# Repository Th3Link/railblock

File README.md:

# RailBlock

[![Firmware License:
GPLv3](https://img.shields.io/badge/Firmware-GPLv3-blue.svg)]()
[![Hardware License: CERN-OHL-S
v2](https://img.shields.io/badge/Hardware-CERN--OHL--S%20v2-orange.svg)]()

**RailBlock** is an open hardware CAN‑bus based block detector and
signal controller for model railways.

It is designed to integrate with a **Raspberry Pi running Rocrail**,
providing reliable **track occupancy detection** and **signal control**
using a distributed CAN bus network.

The project consists of:

-   **Hardware** -- KiCad PCB design
-   **Firmware** -- written in **Embedded Rust** using **Embassy** and
    **heapless**

------------------------------------------------------------------------

# Overview

RailBlock modules are connected using a **50 kbit/s CAN bus** carried
over **RJ45 cables**.\
Each board contains:

-   an **ESP32 microcontroller**
-   a **CAN transceiver**
-   inputs for **Hall sensors**
-   outputs for **signal lights**

Multiple boards can be connected in a **daisy-chain topology**,
distributing both **power (12V)** and **CAN communication** over a
single cable.

Typical setup:

    Raspberry Pi (Rocrail)
            │
       CAN Interface
            │
      ───── CAN Bus ─────
         │       │       │
     RailBlock RailBlock RailBlock
         │       │       │
     Sensors   Signals  Sensors

------------------------------------------------------------------------

# Features

-   CAN bus communication (**50 kbit/s**)
-   RJ45 bus connectors for **daisy chaining**
-   **Power + data on one cable**
-   Up to **3 Hall sensors** per board
-   Up to **7 signal outputs**
-   **ULN2003A sinking driver**
-   **ESP32 microcontroller**
-   **Embedded Rust firmware**
-   **JTAG debugging support**
-   Designed for **Rocrail integration**

------------------------------------------------------------------------

# Hardware

The hardware design is provided as a **KiCad project**.

Each RailBlock node contains:

-   ESP32 microcontroller
-   CAN transceiver
-   ULN2003A output driver
-   connectors for Hall sensors
-   connectors for signal lights
-   two RJ45 bus connectors

The RJ45 connectors allow the bus to **pass through each board**,
simplifying wiring.

Both **power and CAN signals** are carried through the same cable.

------------------------------------------------------------------------

# RJ45 Bus Pinout

RailBlock uses standard **RJ45 connectors** to distribute **CAN bus and
12V power**.

Multiple pins are paralleled to increase current capacity.

    RJ45 Pinout (RailBlock Bus)

       +-----------------------+
       | 1  2  3  4  5  6  7  8 |
       +-----------------------+

    Pin 1  ── GND
    Pin 2  ── GND
    Pin 3  ── GND

    Pin 4  ── CANH
    Pin 5  ── CANL

    Pin 6  ── +12V
    Pin 7  ── +12V
    Pin 8  ── +12V

Notes:

-   Pins **4 and 5 form a twisted pair** in standard Ethernet cables
    (blue / blue‑white).
-   Pins **1--3 and 6--8 are bundled** to increase current carrying
    capacity.
-   This allows moderate **power distribution along the bus**.

------------------------------------------------------------------------

# Bus Topology

RailBlock nodes must be connected in a **linear CAN topology**.

    12V + CAN Bus

    [Terminator] ── RailBlock ── RailBlock ── RailBlock ── [Terminator]

Important:

-   The **first and last node must be terminated**.
-   Termination uses the standard **120 Ω CAN resistor**.

------------------------------------------------------------------------

# Inputs -- Hall Sensors

Each RailBlock board supports **up to 3 Hall sensors** for track
occupancy detection.

Recommended sensor:

-   **TLE4905L**
-   or compatible digital Hall sensors

Typical setup:

-   a small magnet is mounted under a locomotive
-   the Hall sensor detects the magnet
-   the RailBlock node sends an occupancy event

Events are transmitted over CAN using **S88 event messages**.

------------------------------------------------------------------------

# Outputs -- Signals

Each RailBlock board supports **up to 7 signal outputs**.

Outputs are implemented using a **ULN2003A Darlington driver**.

The LED anode connects to **+12V or +5V via a resistor**, while the
RailBlock output sinks current. Some signals have internal resistors.

------------------------------------------------------------------------

# Firmware

The firmware is written in **Embedded Rust**.

Technologies used:

-   **Embassy** async runtime
-   **heapless** containers (no dynamic allocation)
-   **esp-hal**

Design goals:

-   deterministic behaviour
-   low memory usage
-   robust CAN communication

------------------------------------------------------------------------

# CAN Protocol

RailBlock communicates over CAN using two protocol types.

## Märklin CS2 Accessory Protocol

Used for:

-   signal control
-   accessory commands

## S88 Event Messages

Used to report:

-   Hall sensor triggers
-   block occupancy events

------------------------------------------------------------------------

# Programming and Debugging

The ESP32 firmware can be uploaded using:

### Programming Adapter

A dedicated **programming adapter** (separate project).

### JTAG

The board also supports **JTAG debugging**, allowing:

-   breakpoints
-   single stepping
-   real runtime debugging

------------------------------------------------------------------------

# Integration with Rocrail

RailBlock is designed to work with **Rocrail** running on a **Raspberry
Pi**.

Typical architecture:

    Raspberry Pi
       (Rocrail)
           │
       CAN Interface
           │
      ───── CAN Bus ─────
         │       │       │
     RailBlock RailBlock RailBlock
         │       │       │
     Sensors   Signals  Sensors

Rocrail can:

-   receive **occupancy events**
-   control **signals and accessories**

------------------------------------------------------------------------

# Repository Structure

    railblock/
    │
    ├─ firmware/        Embedded Rust firmware
    │
    ├─ hardware/        KiCad PCB design
    │
    ├─ docs/            Documentation
    │
    └─ README.md

------------------------------------------------------------------------

# Licensing

This repository contains both **hardware designs** and **software**.

## Firmware

Licensed under:

**GNU General Public License v3 (GPLv3)**

See:

    firmware/LICENSE.txt

## Hardware

Licensed under:

**CERN Open Hardware Licence Version 2 -- Strongly Reciprocal
(CERN-OHL-S-2.0)**

See:

    hardware/LICENSE.txt

------------------------------------------------------------------------

# Status

Early development.

Hardware and firmware are evolving together.

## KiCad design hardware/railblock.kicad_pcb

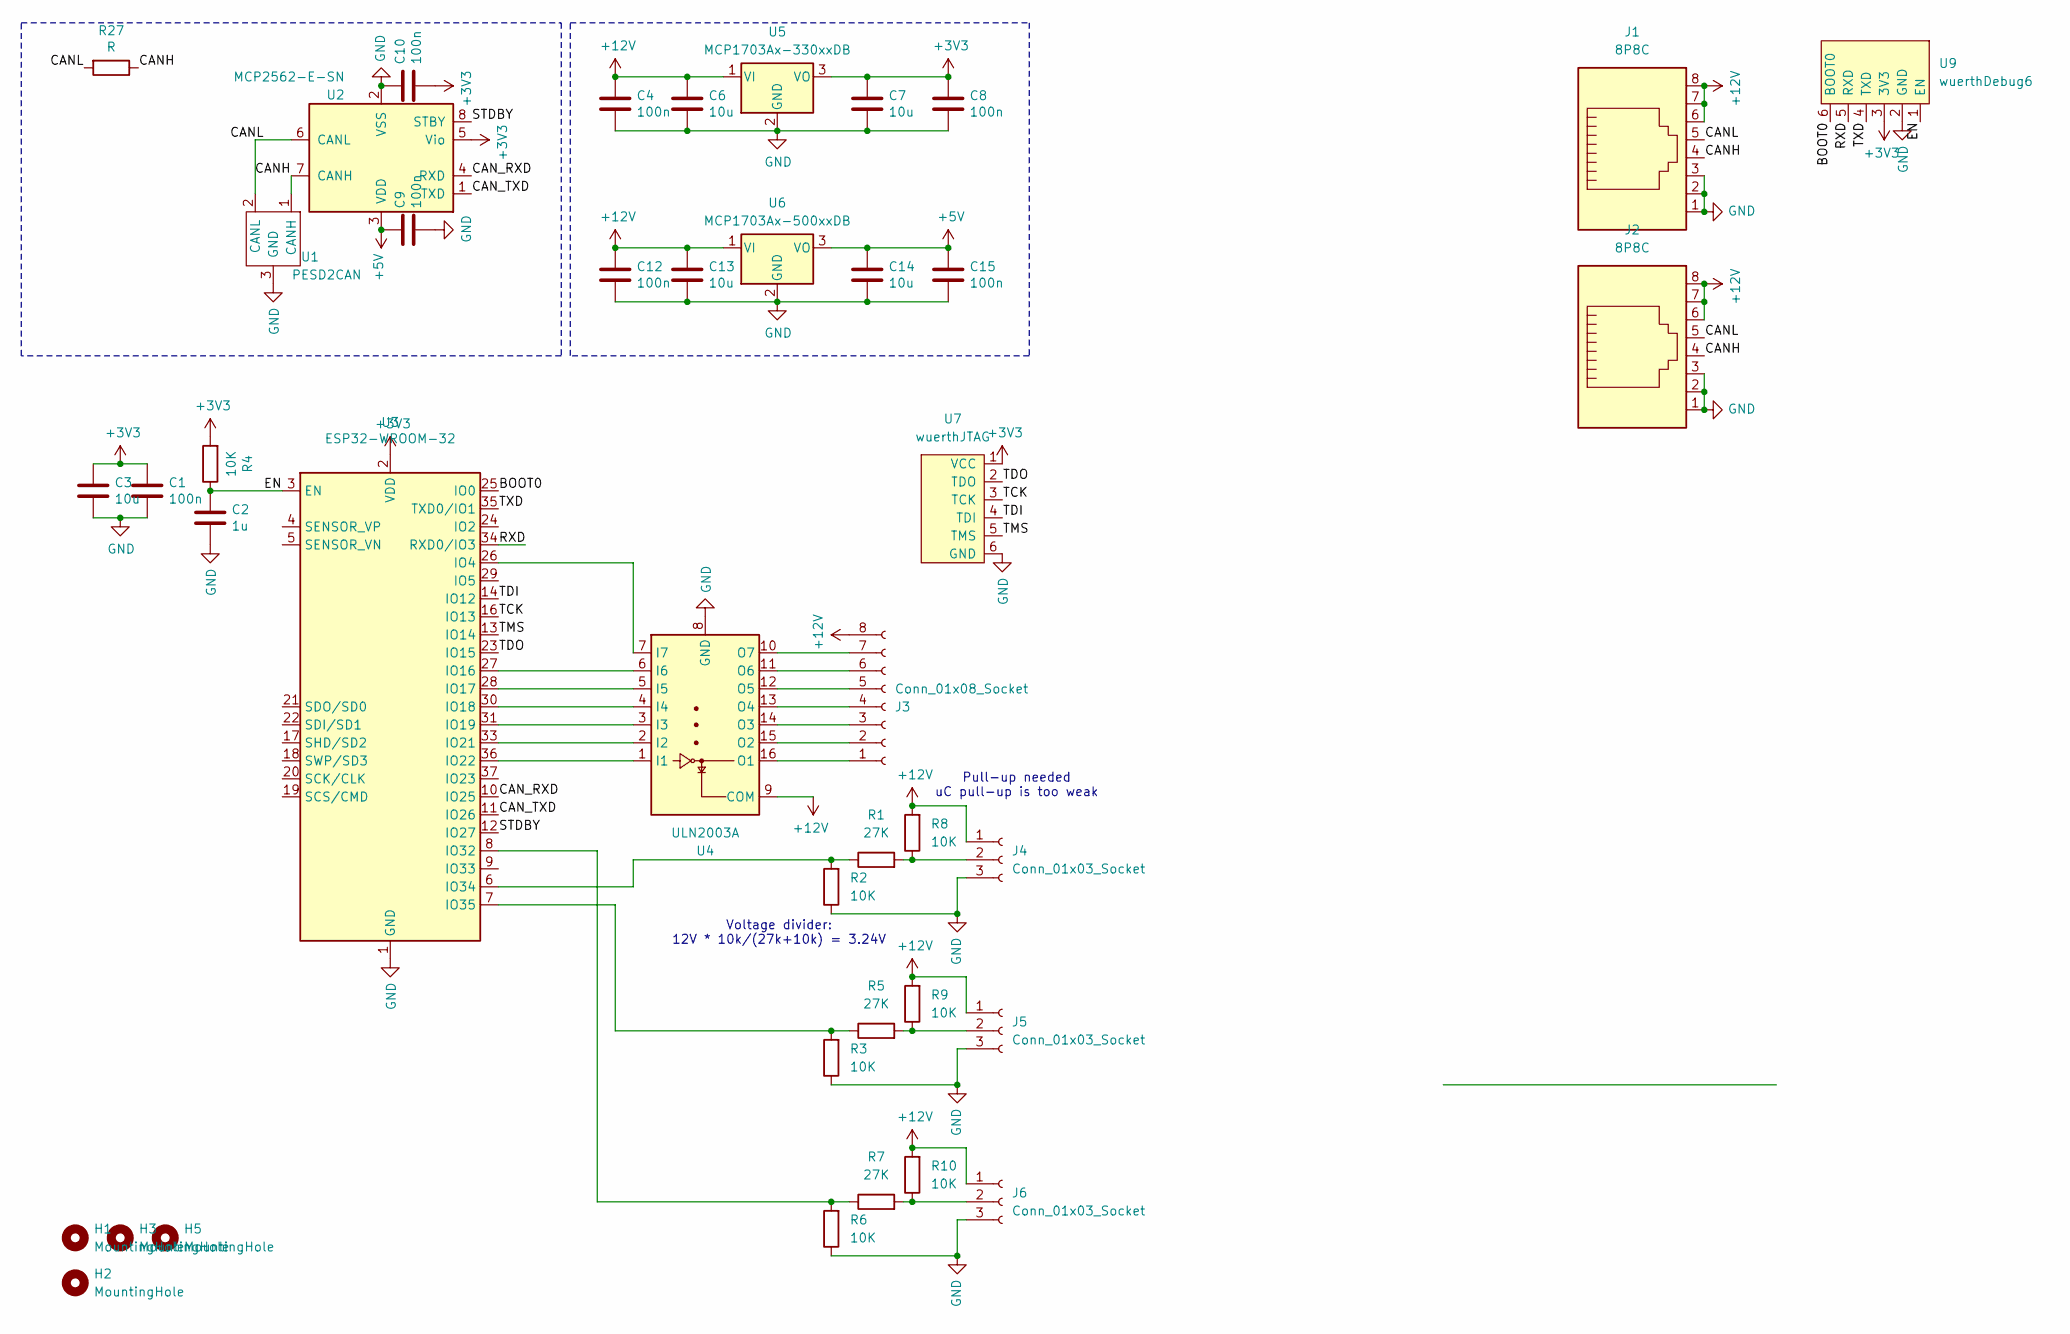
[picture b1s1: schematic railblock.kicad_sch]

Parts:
C1, C4, C8, C9, C10, C12, C15: 100n; C_0603_1608Metric_Pad1.08x0.95mm_HandSolder
C2: 1u; C_0603_1608Metric_Pad1.08x0.95mm_HandSolder
C3, C6, C7, C13, C14: 10u; C_0805_2012Metric_Pad1.18x1.45mm_HandSolder
H1, H2, H3, H5: MountingHole; MountingHole_3.2mm_M3_DIN965
J1, J2: 8P8C; RJ45_Ninigi_GE
J3: Conn_01x08_Socket; WAGO250-208
J4, J5, J6: Conn_01x03_Socket; WAGO250-203
R1, R5, R7: 27K; R_0603_1608Metric_Pad0.98x0.95mm_HandSolder
R2, R3, R4, R6, R8, R9, R10: 10K; R_0603_1608Metric_Pad0.98x0.95mm_HandSolder
R27: R; R_0603_1608Metric_Pad0.98x0.95mm_HandSolder
U1: PESD2CAN; SOT-23
U2: MCP2562-E-SN; SOIC-8_3.9x4.9mm_P1.27mm
U3: ESP32-WROOM-32
U4: ULN2003A; SOIC-16_3.9x9.9mm_P1.27mm
U5: MCP1703Ax-330xxDB; SOT-223-3_TabPin2
U6: MCP1703Ax-500xxDB; SOT-223-3_TabPin2
U7: wuerthJTAG
U9: wuerthDebug6

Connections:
+3V3: C1.1, C3.1, C7.1, C8.1, C10.1, R4.2, U2.5 (Vio), U3.2 (VDD), U5.3 (VO), U7.1 (VCC), U9.3 (3V3)
+5V: C9.1, C14.1, C15.1, U2.3 (VDD), U6.3 (VO)
+12V: C4.1, C6.1, C12.1, C13.1, J1.6, J1.7, J1.8, J2.6, J2.7, J2.8, J3.8, J4.1, J5.1, J6.1, R8.2, R9.2, R10.2, U4.9 (COM), U5.1 (VI), U6.1 (VI)
/BOOT0: U3.25 (IO0), U9.6 (BOOT0)
/CANH: J1.4, J2.4, R27.1, U1.1 (CANH), U2.7 (CANH)
/CANL: J1.5, J2.5, R27.2, U1.2 (CANL), U2.6 (CANL)
/CAN_RXD: U2.4 (RXD), U3.10 (IO25)
/CAN_TXD: U2.1 (TXD), U3.11 (IO26)
/EN: C2.1, R4.1, U3.3 (EN), U9.1 (EN)
/RXD: U3.34 (RXD0/IO3), U9.5 (RXD)
/STDBY: U2.8 (STBY), U3.12 (IO27)
/TCK: U3.16 (IO13), U7.3 (TCK)
/TDI: U3.14 (IO12), U7.4 (TDI)
/TDO: U3.23 (IO15), U7.2 (TDO)
/TMS: U3.13 (IO14), U7.5 (TMS)
/TXD: U3.35 (TXD0/IO1), U9.4 (TXD)
GND: C1.2, C2.2, C3.2, C4.2, C6.2, C7.2, C8.2, C9.2, C10.2, C12.2, C13.2, C14.2, C15.2, J1.1, J1.2, J1.3, J2.1, J2.2, J2.3, J4.3, J5.3, J6.3, R2.1, R3.1, R6.1, U1.3 (GND), U2.2 (VSS), U3.1 (GND), U3.15 (GND), U3.38 (GND), U3.39 (GND), U4.8 (GND), U5.2 (GND), U6.2 (GND), U7.6 (GND), U9.2 (GND)
unnamed: J3.1, U4.16 (O1)
unnamed: J3.2, U4.15 (O2)
unnamed: J3.3, U4.14 (O3)
unnamed: J3.4, U4.13 (O4)
unnamed: J3.5, U4.12 (O5)
unnamed: J3.6, U4.11 (O6)
unnamed: J3.7, U4.10 (O7)
unnamed: J4.2, R1.2, R8.1
unnamed: J5.2, R5.2, R9.1
unnamed: J6.2, R7.2, R10.1
unnamed: U3.26 (IO4), U4.7 (I7)
unnamed: U3.27 (IO16), U4.6 (I6)
unnamed: U3.28 (IO17), U4.5 (I5)
unnamed: U3.30 (IO18), U4.4 (I4)
unnamed: U3.31 (IO19), U4.3 (I3)
unnamed: U3.33 (IO21), U4.2 (I2)
unnamed: U3.36 (IO22), U4.1 (I1)
unnamed: R6.2, R7.1, U3.8 (IO32)
unnamed: R1.1, R2.2, U3.6 (IO34)
unnamed: R3.2, R5.1, U3.7 (IO35)

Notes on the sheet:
Voltage divider: 12V * 10k/(27k+10k) = 3.24V
Pull-up needed uC pull-up is too weak

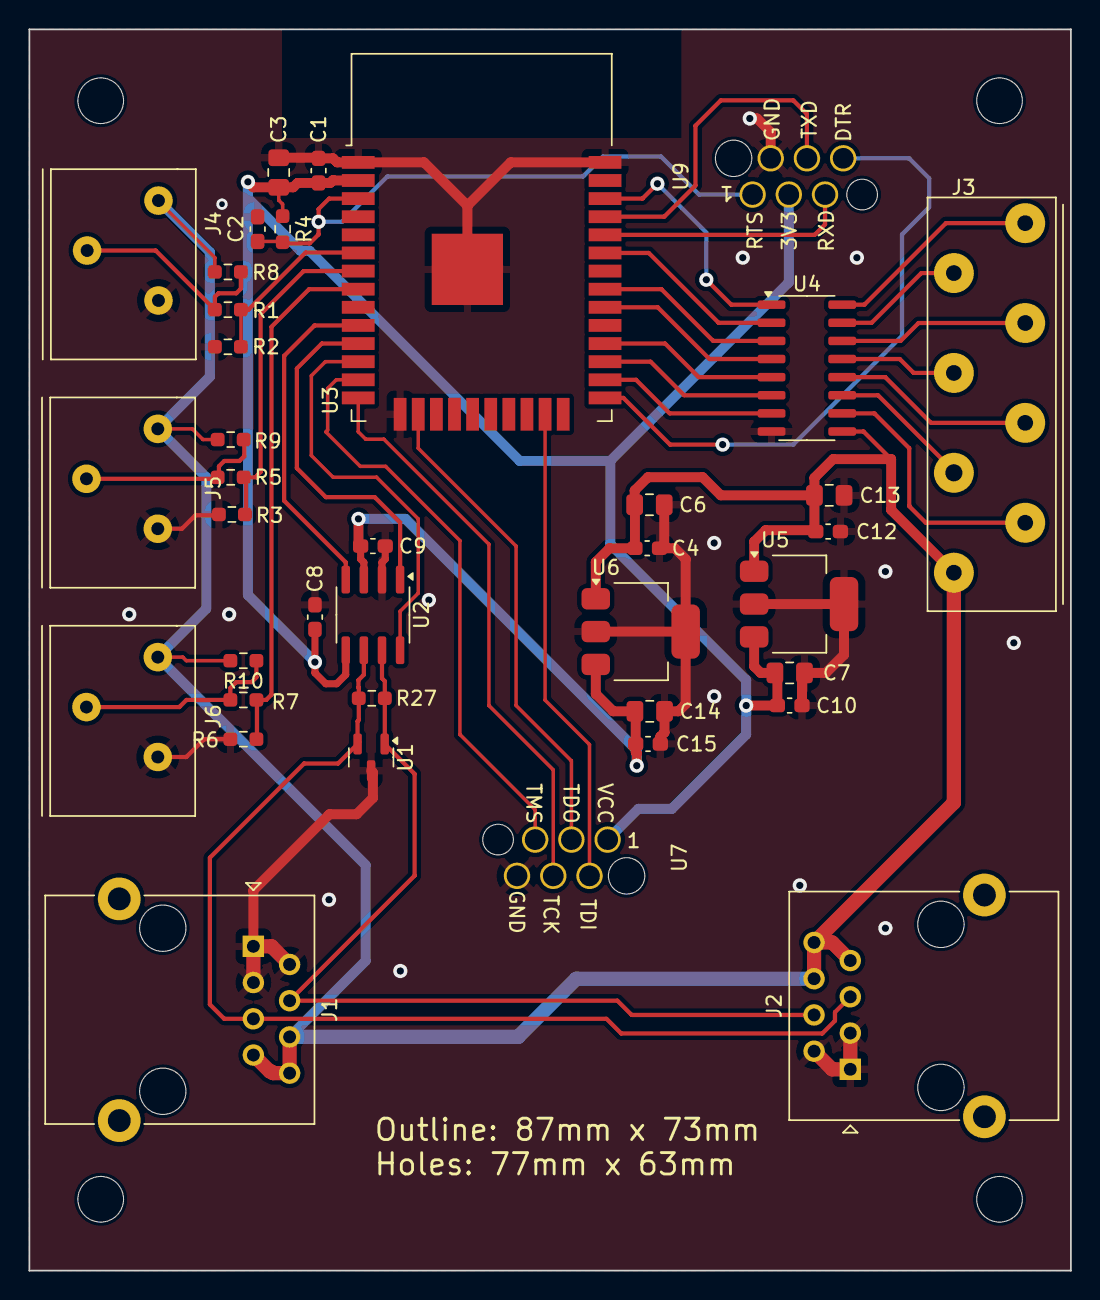
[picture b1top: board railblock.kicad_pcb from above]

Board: 2 copper layers, 73.0 x 87.0 mm, 42 parts (0 on the bottom side), 37 nets.

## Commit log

2025-03-12 feat: Add initial files
2025-03-21 fix: Make it work
2025-03-24 feat: Add devicetype
2026-01-01 feat: Make hall and relais working
2026-01-26 feat: Move implementation to rust
2026-03-13 fix: Adapt accessory and S88 data format
2026-03-13 fix: Add pull-up for hall sensors
2026-03-13 feat: Add JTAG interface
2026-03-13 feat: Bring more structure into the project
